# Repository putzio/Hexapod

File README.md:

# Hexapod

This is a project of a remotely controlled walking robot. 
If you click the link bellow you can see the movie, which shows how the robot walks:
https://photos.app.goo.gl/Wpt8i5VjzHMQxFu78

## The project consists of 4 main parts: 

### Mechanical construction
I have designed the robot in Fusin 360, which allows to generate a link to the CAD model:

https://a360.co/3f0cuEE

### Electronics
The .sch and .brd files are located in the documentation directory

### Mobile App
to control the robot I have created a simple application:

https://gallery.appinventor.mit.edu/?galleryid=f348ef10-de80-403b-b9b3-069c0fd0a535

### C++ code for the raspberry pi pico

the main file is hexapod.cpp. It uses classes Servo, Leg and Body, which are included in the lib directory

If you woul like to build it on your own you can use VSC and configure your computer as it is shown in the link below:
https://www.youtube.com/watch?v=B5rQSoOmR5w

## Bachelor thesis 
I have described this project in my bachelor thesis and you can read it in the documentation directory (unfortunately it's in polish)  
##  Unity simulation
I have also created a simulation in Unity (using an older version of my mechanical construction), so you can check it out in my other repository:
https://github.com/putzio/Hexapod_Unity

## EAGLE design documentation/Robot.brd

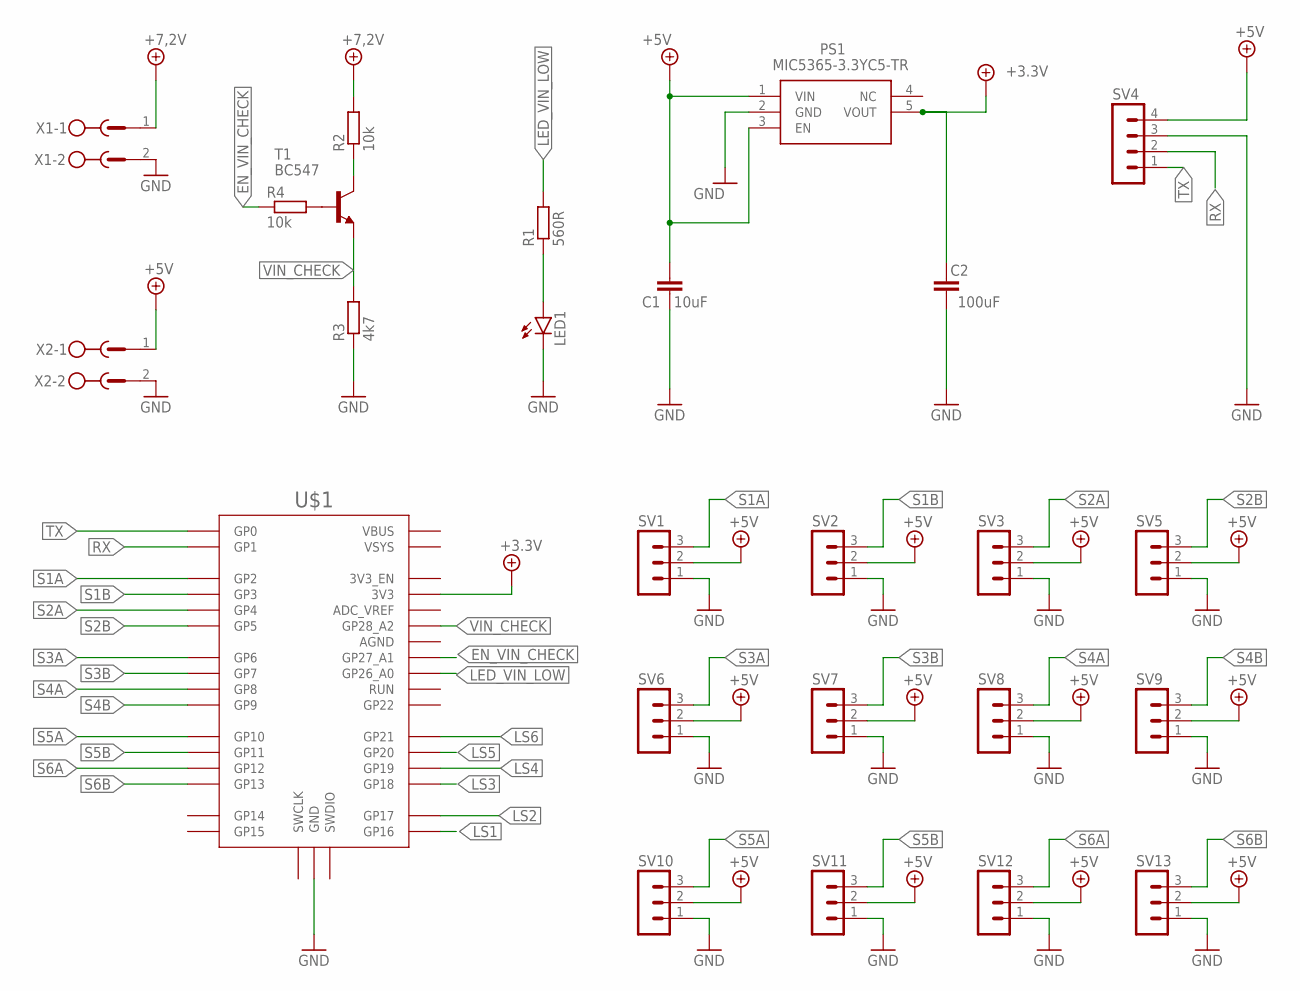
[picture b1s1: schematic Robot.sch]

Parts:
C1: 10uF; C1206
C2: 100uF; C1206
LED1: LEDCHIPLED_1206; CHIPLED_1206
PS1: MIC5365-3.3YC5-TR; SOT65P210X110-5N
R1: 560R; R1206
R2: 10k; R1206
R3: 4k7; R1206
R4: 10k; 0204/7
SV1, SV2, SV3, SV5, SV6, SV7, SV8, SV9, SV10, SV11, SV12, SV13: MA03-1
SV4: MA04-1
T1: BC547; TO92
U$1: RPI_PICO-TH; RPI_PICO_TH
X1, X2: MSTBV2

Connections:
+3.3V: C2.2, PS1.5 (VOUT), U$1.3V3
+5V: C1.2, PS1.1 (VIN), PS1.3 (EN), SV1.2, SV2.2, SV3.2, SV4.4, SV5.2, SV6.2, SV7.2, SV8.2, SV9.2, SV10.2, SV11.2, SV12.2, SV13.2, X2.1
+9V: R2.2, X1.1
EN_VIN_CHECK: R4.1, U$1.GP27_A1
GND: C1.1, C2.1, LED1.C, PS1.2 (GND), R3.1, SV1.1, SV2.1, SV3.1, SV4.3, SV5.1, SV6.1, SV7.1, SV8.1, SV9.1, SV10.1, SV11.1, SV12.1, SV13.1, U$1.GND@1 (GND), U$1.GND@2 (GND), U$1.GND@3 (GND), U$1.GND@4 (GND), U$1.GND@5 (GND), U$1.GND@6 (GND), U$1.GND@7 (GND), U$1.GND@8 (GND), X1.2, X2.2
LED_VIN_LOW: R1.2, U$1.GP26_A0
LS1: U$1.GP16
LS2: U$1.GP17
LS3: U$1.GP18
LS4: U$1.GP19
LS5: U$1.GP20
LS6: U$1.GP21
unnamed: LED1.A, R1.1
unnamed: R2.1, T1.3 (C)
unnamed: R4.2, T1.2 (B)
RX: SV4.2, U$1.GP1
S1A: SV1.3, U$1.GP2
S1B: SV2.3, U$1.GP3
S2A: SV3.3, U$1.GP4
S2B: SV5.3, U$1.GP5
S3A: SV6.3, U$1.GP6
S3B: SV7.3, U$1.GP7
S4A: SV8.3, U$1.GP8
S4B: SV9.3, U$1.GP9
S5A: SV10.3, U$1.GP10
S5B: SV11.3, U$1.GP11
S6A: SV12.3, U$1.GP12
S6B: SV13.3, U$1.GP13
TX: SV4.1, U$1.GP0
VIN_CHECK: R3.2, T1.1 (E), U$1.GP28_A2

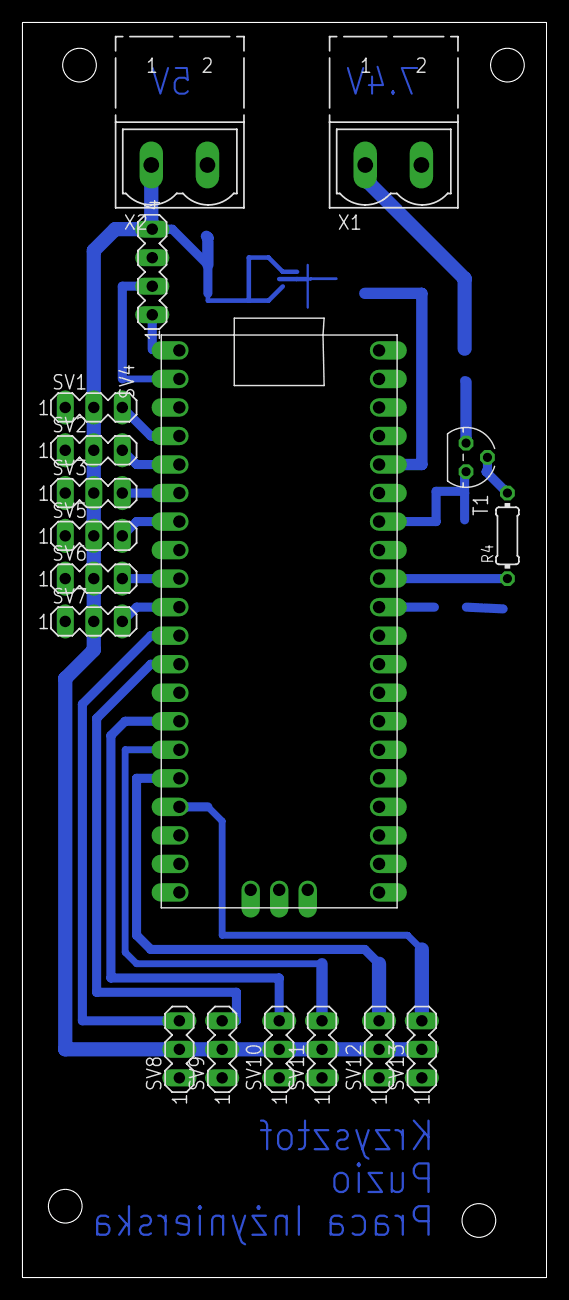
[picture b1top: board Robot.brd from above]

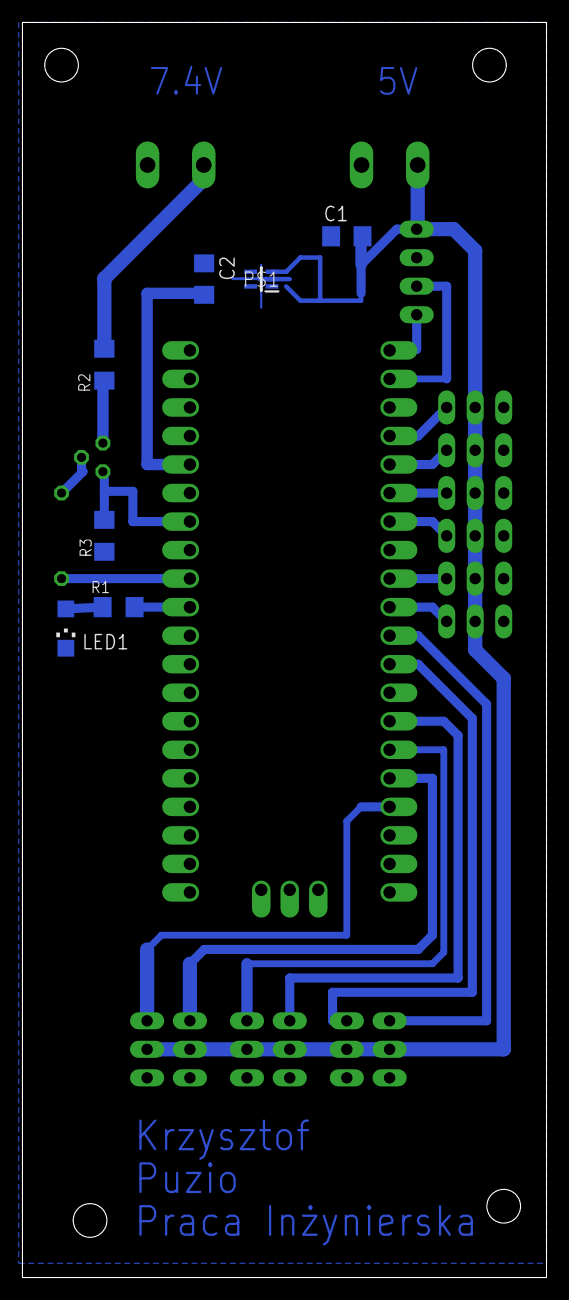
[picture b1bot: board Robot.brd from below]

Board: 2 copper layers, 46.7 x 111.8 mm, 25 parts (7 on the bottom side), 24 nets.

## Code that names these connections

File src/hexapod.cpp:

#include <stdio.h>
#include "pico/stdlib.h"
#include "hardware/pwm.h"
#include "pico/double.h"
#include "hardware/clocks.h"
#include "hardware/uart.h"
#include "hardware/irq.h"
#include "hardware/adc.h"
#include "hardware/gpio.h"
#include "Servo.h"
#include "Leg.hpp"
#include "Body.hpp"

//----------------------my program-------------------------------------------------
#define UART_ID uart0
#define BAUD_RATE 9600

#define ARRAY_SIZE(a) sizeof(a) / sizeof(a[0])

// pins
#define RX_PIN 1
#define TX_PIN 0
// Servos - 2-13
#define LED_VIN_LOW 26
#define EN_VIN_CHECK 27
#define VIN_CHECK_GPIO 28
#define VIN_CHECK_A_INPUT (VIN_CHECK_GPIO - 26)
#define BUILD_IN_LED 25

#define LED_PIN 15

// Measure Battery
#define RESISTOR_3 4700          // OHM
#define RESISTOR_2 10000         // OHM
#define RP_VOLTAGE 3.3           // V
#define MIN_BATTERY_VOLATAGE 7.0 // V
#define ADC_MAX 4096             // 12-bit
#define RESISTOR_3_MIN_VOLTAGE (MIN_BATTERY_VOLATAGE / (RESISTOR_2 + RESISTOR_3) * RESISTOR_3)
#define MIN_ADC_VALUE (RESISTOR_3_MIN_VOLTAGE * ADC_MAX / RP_VOLTAGE)

const int16_t SERVO_CALIB[12] = {
    155,
    -60,
    -155,
    -80,
    20,
    95,
    -30,
    60,
    55,
    -70,
    90,
    -50};

void OnUartRx();
void UART_INIT()
{
    uart_init(uart0, BAUD_RATE);

    // Set the GPIO pin mux to the UART - 0 is TX, 1 is RX
    gpio_set_function(RX_PIN, GPIO_FUNC_UART);
    gpio_set_function(TX_PIN, GPIO_FUNC_UART);

    // interrupts
    //  Set up a RX interrupt
    //  We need to set up the handler first
    //  Select correct interrupt for the UART we are using
    int UART_IRQ = UART_ID == uart0 ? UART0_IRQ : UART1_IRQ;

    // And set up and enable the interrupt handlers
    irq_set_exclusive_handler(UART_IRQ, OnUartRx);
    irq_set_enabled(UART_IRQ, true);

    // Now enable the UART to send interrupts - RX only
    uart_set_irq_enables(UART_ID, true, false);
}
bool changeVelocity = false;
int velocity = MIN_VELOCITY;
bool velocityChanged = false;
void OnUartRx() // bool *changeVelocity, *velocityChanged, *velocity, *mode
{
    //----------getting the robot moves-----------------

    while (uart_is_readable(UART_ID))
    {
        char recMode = uart_getc(UART_ID);
        uart_puts(uart0, "Recieved:\n");
        uart_putc(uart0, recMode);
        uart_puts(uart0, "\n");
        if (changeVelocity)
        {
            if (recMode == '&')
            {
                velocityChanged = true;
                changeVelocity = false;
            }
            else
            {
                velocity *= 10;
                velocity += (int)recMode - 48;
            }
        }
        else
        {
            switch (recMode)
            {
            case 'f':
                mode = ForwardMode;
                break;
            case 'b':
                mode = BackMode;
                break;
            case 'l':
                mode = LeftMode;
                break;
            case 'r':
                mode = RightMode;
                break;
            case 's':
                mode = StopMode;
                break;
            case 'R':
                mode = ResetMode;
                break;
            case 'P':
                mode = Pos90Mode;
                break;
            case 'V':
            {
                changeVelocity = true;
                velocity = 0;
                break;
            }
            }
        }
    }
    //----------echo-------------------
    // char buffer[20];
    // int chars_rxed = 0;
    // while (uart_is_readable(UART_ID)) {
    //     buffer[chars_rxed] = uart_getc(UART_ID);
    //     chars_rxed++;
    //     if(chars_rxed>=20)
    //         break;
    // }
    // for(int i = 0; i <= chars_rxed; i++)
    //     if (uart_is_writable(UART_ID))
    //     {
    //         uart_putc(UART_ID, buffer[i]);
    //     }
    // uart_putc(UART_ID,10);
}

void ADC_INIT()
{
    // init ADC
    adc_init();
    // // Make sure GPIO is high-impedance, no pullups etc
    adc_gpio_init(VIN_CHECK_GPIO);
    // Select ADC input 0 (GPIO26)
    adc_select_input(VIN_CHECK_A_INPUT);
    // set LED and gpio, which turns on the transistor as output
    gpio_init(LED_VIN_LOW);
    gpio_set_dir(LED_VIN_LOW, GPIO_OUT);
    // gpio_put(LED_VIN_LOW,1);
    gpio_init(EN_VIN_CHECK);
    gpio_set_dir(EN_VIN_CHECK, GPIO_OUT);
    gpio_init(BUILD_IN_LED);
    gpio_set_dir(BUILD_IN_LED, GPIO_OUT);
}
bool MeasureBattery()
{
    // turn on the transistor
    gpio_put(EN_VIN_CHECK, 1);
    sleep_ms(100);
    // measure voltage
    uint16_t result = adc_read();
    gpio_put(EN_VIN_CHECK, 0);
    if (result < MIN_ADC_VALUE)
    {
        for (int i = 0; i < 3; i++)
        {
            gpio_put(LED_VIN_LOW, 1);
            gpio_put(BUILD_IN_LED, 1);
            sleep_ms(500);
            gpio_put(LED_VIN_LOW, 0);
            gpio_put(BUILD_IN_LED, 0);
            sleep_ms(500);
        }
        return false;
    }
    return true;
}

int main()
{
    stdio_init_all();

    gpio_init(BUILD_IN_LED);
    gpio_set_dir(BUILD_IN_LED, GPIO_OUT);

    UART_INIT();
    ADC_INIT();
    MeasureBattery();

    uint8_t mser[6], sser[6];
    for (int i = 0; i < ARRAY_SIZE(mser); i++)
    {
        mser[i] = 2 * (i + 1); //(i+1) because we start at gpio 2
        sser[i] = 2 * (i + 1) + 1;
    }

    Body body(mser, sser, SERVO_CALIB);

    if (MeasureBattery())
        body.ModeChanged(mode);

    while (1)
    {
        if (!MeasureBattery())
        {
            body.DisableLegs();
            sleep_ms(10000);
        }
        else
        {
            if (velocityChanged)
            {
                body.ChangeBodyVelocityLimits(velocity);
            }
            // enableProgram = MeasureBattery();
            if (mode != body.modeType)
            {
                body.ModeChanged(mode);
            }
            gpio_put(BUILD_IN_LED, 1);
            do
            {
                body.Move();
                sleep_ms(20); // 20
            } while (!body.MovesDone());

            gpio_put(BUILD_IN_LED, 0);
        }
        sleep_ms(20);
    }
}

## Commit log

2021-12-09 Servo objects
2021-12-25 Bluetooth control of servo, range 90-110
2021-12-25 velocity, but does not move
2021-12-26 Velotity and acceleration works
2022-01-04 Opposite legs
2022-01-05 enum Mode
2022-01-05 new enum Works
2022-01-05 Need to fix
2022-01-05 LoopMaster/LoopSlave
2022-01-06 Left/Right, increased velocity, middle legs go the opposite way
2022-01-07 velocity change and battery check improv
2022-01-10 slaveServo
2022-01-11 problems with 10-12 gpio
2022-01-16 calibration to test
2022-01-18 Valibration Values
2022-01-21 Works, just need to change SlaveServo
2022-01-22 Final version?
2022-01-27 Last commit?
2022-02-04 Extra files: .sch, .brd, CAD and my thesis
2022-02-23 cmake
2022-02-23 Change of the main file and split it to seperated files
2022-02-23 serperate documentation directory
2022-02-23 deleted basic config example
2022-02-23 Links to the Bluetooth app and the movie with the created robot
2022-08-14 cleaning unnecessary stuff
2022-08-14 change .gitignore
2022-08-15 CMakeLists.txt update
2022-09-18 pwm_driver
2022-09-18 Servo inherits from pwm_driver
2022-09-18 Servo in seperate files
